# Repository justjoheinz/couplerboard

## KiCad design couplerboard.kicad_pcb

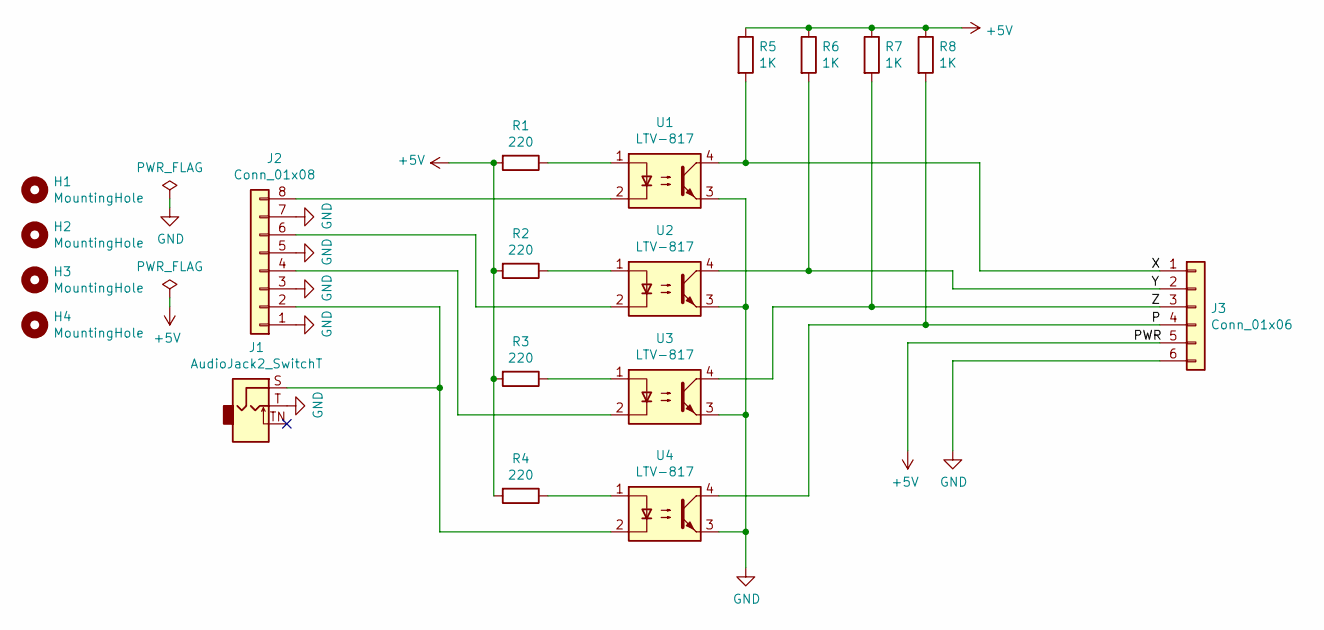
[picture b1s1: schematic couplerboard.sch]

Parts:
H1, H2, H3, H4: MountingHole; MountingHole_3.2mm_M3_DIN965
J1: AudioJack2_SwitchT; ThonkIcon
J2: Conn_01x08; TerminalBlock_MetzConnect_Type094_RT03506HBLU_1x08_P5.00mm_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
J3: Conn_01x06; TerminalBlock_MetzConnect_Type094_RT03506HBLU_1x06_P5.00mm_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
R1, R2, R3, R4: 220; R_Axial_DIN0207_L6.3mm_D2.5mm_P7.62mm_Horizontal
R5, R6, R7, R8: 1K; R_Axial_DIN0207_L6.3mm_D2.5mm_P7.62mm_Horizontal
U1, U2, U3, U4: LTV-817; DIP-4_W7.62mm

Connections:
+5V: J3.5, R1.2, R2.2, R3.2, R4.2, R5.1, R6.1, R7.1, R8.1
/P: J3.4, R8.2, U4.4
/X: J3.1, R5.2, U1.4
/Y: J3.2, R6.2, U2.4
/Z: J3.3, R7.2, U3.4
GND: J1.T, J2.1, J2.3, J2.5, J2.7, J3.6, U1.3, U2.3, U3.3, U4.3
unnamed: J1.S, J2.2, U4.2
unnamed: J2.4, U3.2
unnamed: J2.6, U2.2
unnamed: J2.8, U1.2
unnamed: R1.1, U1.1
unnamed: R2.1, U2.1
unnamed: R3.1, U3.1
unnamed: R4.1, U4.1

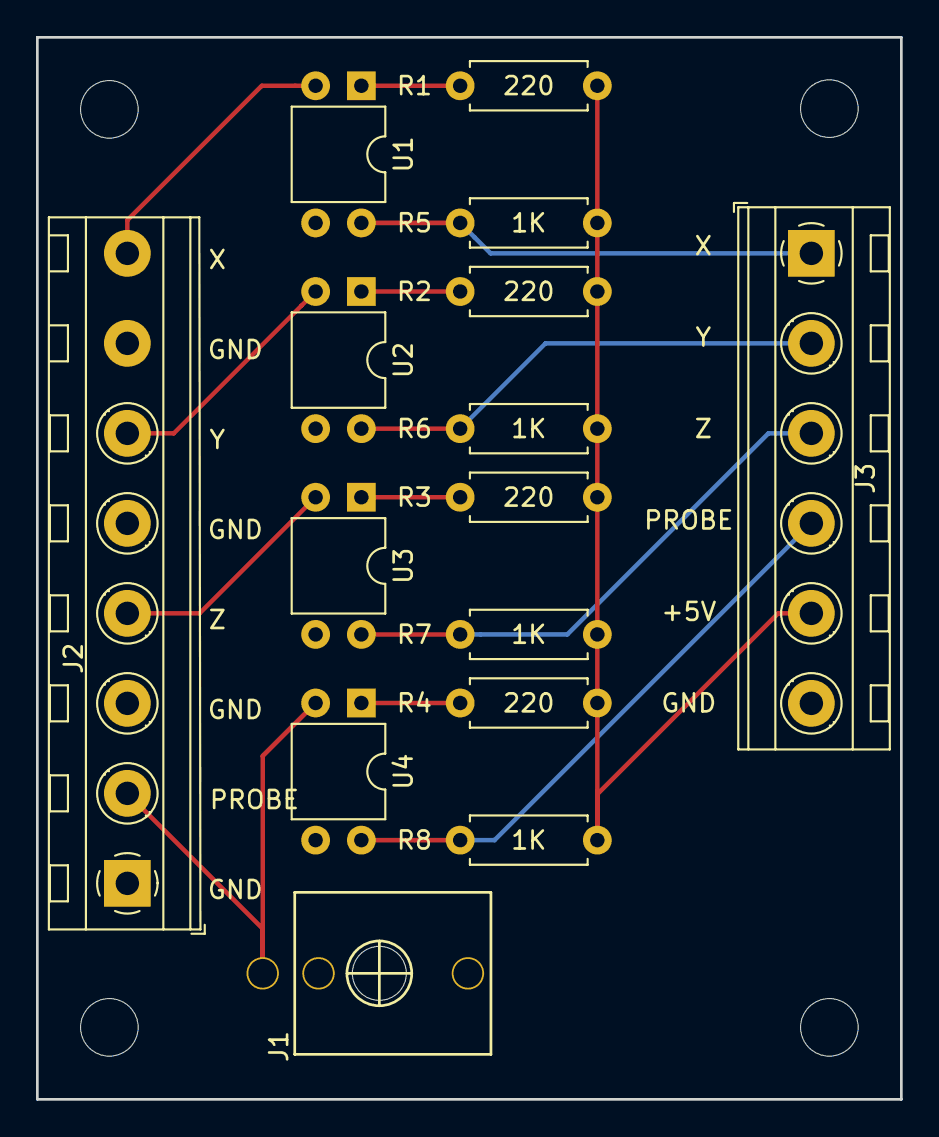
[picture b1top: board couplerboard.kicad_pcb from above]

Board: 2 copper layers, 48.0 x 59.0 mm, 19 parts (0 on the bottom side), 14 nets.

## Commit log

2020-05-13 First version
2020-05-13 Fix missing route
2020-05-14 Added mono jack for probe
2020-05-14 Reannotate
